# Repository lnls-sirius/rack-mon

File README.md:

# Controls Group rack monitoring system

## Index

- [Description](https://github.com/lnls-sirius/rack-mon#description)
- [Software](https://github.com/lnls-sirius/rack-mon#software)
- [Installation](https://github.com/lnls-sirius/rack-mon#installation)
- [Versions](https://github.com/lnls-sirius/rack-mon#versions)

## Description

   This project is a hardware and software solution for Sirius cabinets monitoring based in a NXP's development platform, FRDM-KL25z, and SPIxxCON bus present  on Controls Group SERIALxxCON hardware. The designed baseboard for NXP development  platform  contains  the  necessary  peripherals  to  acquire  information  such  as temperature, humidity, fan status, door status and supply voltage in order to predict possible system failures and evaluate its correlation with the acquired data.

   It also contains an adapter that [enables this project to work with mbed LPC1768](https://github.com/lnls-sirius/rack-mon/tree/master/KL25Z_to_LPC1768) in instead of KL25z.

## Software

### [KL25z](https://github.com/lnls-sirius/rack-mon/blob/master/Software/SlaveSW/SlaveKL25Z.c)

   A C program written through Mbed's platform divided in 3 modes:

   * Read mode

   An interruption associated with the rising border of Slave Select signal. In this interruption the microcontroller reads the SPI buffer and if a command other than zero is found stores the command.

   * Buffer copy

   The main loop in the program, where the strings are copied to the "answer" buffer according to the code read in the Read Mode.

   * Ansawer mode

   Another interruption associated with Slave Select signal, but this happens in the falling border of the signal. This is where the board replies the requested value through SPI.

### [LPC1768](https://github.com/lnls-sirius/rack-mon/blob/master/KL25Z_to_LPC1768/Software/SlaveLPC1768.cpp)

   When using LPC1768 in instead of KL25Z a few things change. The principle is still the same: reading from the SPI, copying to a answer buffer and responding through SPI but here the program doesn't work with interruptions, everything happens inside the main loop.

   The microcontroller reads the SPI and if there is any request enters a switch-case conditional. If the command corresponds to any of the known commands, LPC1768 responds accordingly.

### [BeagleBone Black](https://github.com/lnls-sirius/rack-mon/blob/master/Software/MasterSW/MasterBBB.py)

   A Python script responsible for the communication between BeagleBone Black and KL25z (or LPC1768) through SPI and for providing the data to multiple workstations through TCP/IP sockets.

#### Configuration and Python3 module

In order to operate the board you should first do the following configurations in your SERIALxxCON:

- Configure the SPI buses with:

```shell
config-pin P9_17 spi_cs
config-pin P9_21 spi
config-pin P9_18 spi
config-pin P9_22 spi_sclk
```
- Write the previous commands on `/etc/rc.local` if desired

- Stop bbb-function script with:

```shell
systemctl stop bbb-function
```
- Disable bbb-function if desired:

```shell
systemctl disable bbb-function
```

A python3 module was developed in order to simplify the SPI requests to the board. The [Very Simple Protocol](https://gitlab.cnpem.br/vitor.santos/racks/blob/master/Software/MasterSW/vsp.py) module functions are:

- send(char, timeout_ms = 1)

sends a character to the monitoring board and returns a string with its response

- get(\*args)

sends multiple characters to the monitoring board and returns a list with it's response _in order_

- get_all()

returns a list with values for supply voltage, fan status, DHT's temperature measurement, fan current, humidity, LM35's temperature measurement, back door status and front door status _in that order_

- get_LM35()

returns LM35's temperature measurement

- get_DHT()

returns the boards DHT's temperature measurement

- get_humidity()

returns humidity value

- get_fdoor()

returns front door status

- get_bdoor()

returns back door status

- get_fanstat()

returns fan status

- get_current()

returns current measurement

- get_voltage()

returns supply voltage

- isBoard()

works only with LPC1768 and returns the software version, if "None" is returned it means probably there's no board connected or it's a KL25z with software version < v1.60

If using KL25z in instead of LPC1768, lines containing "for i in range (10)" should be changed to "for i in range(11)".

## Installation

   * Remove the back panel of SERIALxxCON box and place the SPIxxCON - RJ25 adapter. Connect the serial cable and close the box with the [new back panel](https://gitlab.cnpem.br/vitor.santos/racks/blob/master/Hardware/SPIxxCON_BackPanel.pdf).

   * Plug one end of the power cable into the black plug and the other end into the power strip.

   * Unplug the fan power cable from the power strip and plug it into the box's red power outlet.

   * Fix the magnetic sensors to their mountings and place them close to the door, in the upper part of the cabinet. Place the neodymium magnet on the cabinet door in a way that when its closed the magnet is close to the magnetic sensor.

   * Place the DHT11 humidity sensor close to the box.

   * Place the LM35 temperature sensor wherever you want.

   * Connect all the sensors to their respective connectors.

## Versions

Each prototype version is named as follows:
_vX.YZ_
- X: hardware version (even numbers are in-house manufactured prototypes).
- Y: prototype hardware version.
- Z: software version.

Available KL25z software versions:

- [v0.60](https://github.com/lnls-sirius/rack-mon/blob/master/Software/SlaveSW/SlaveKL25Z.c)
- ~~v0.58~~
- ~~v0.55~~
- ~~v0.5~~
- ~~v0.4~~

Available LPC1768 software versions:

- [v1.60](https://github.com/lnls-sirius/rack-mon/blob/master/KL25Z_to_LPC1768/Software/SlaveLPC1768.cpp)

Previous versions can be found on these repositories: [KL25Z](https://os.mbed.com/users/vitorsp/code/rack-monitoring-system/) and [LPC1768](https://os.mbed.com/users/vitorsp/code/rack-monitoring-system-LPC1768/).

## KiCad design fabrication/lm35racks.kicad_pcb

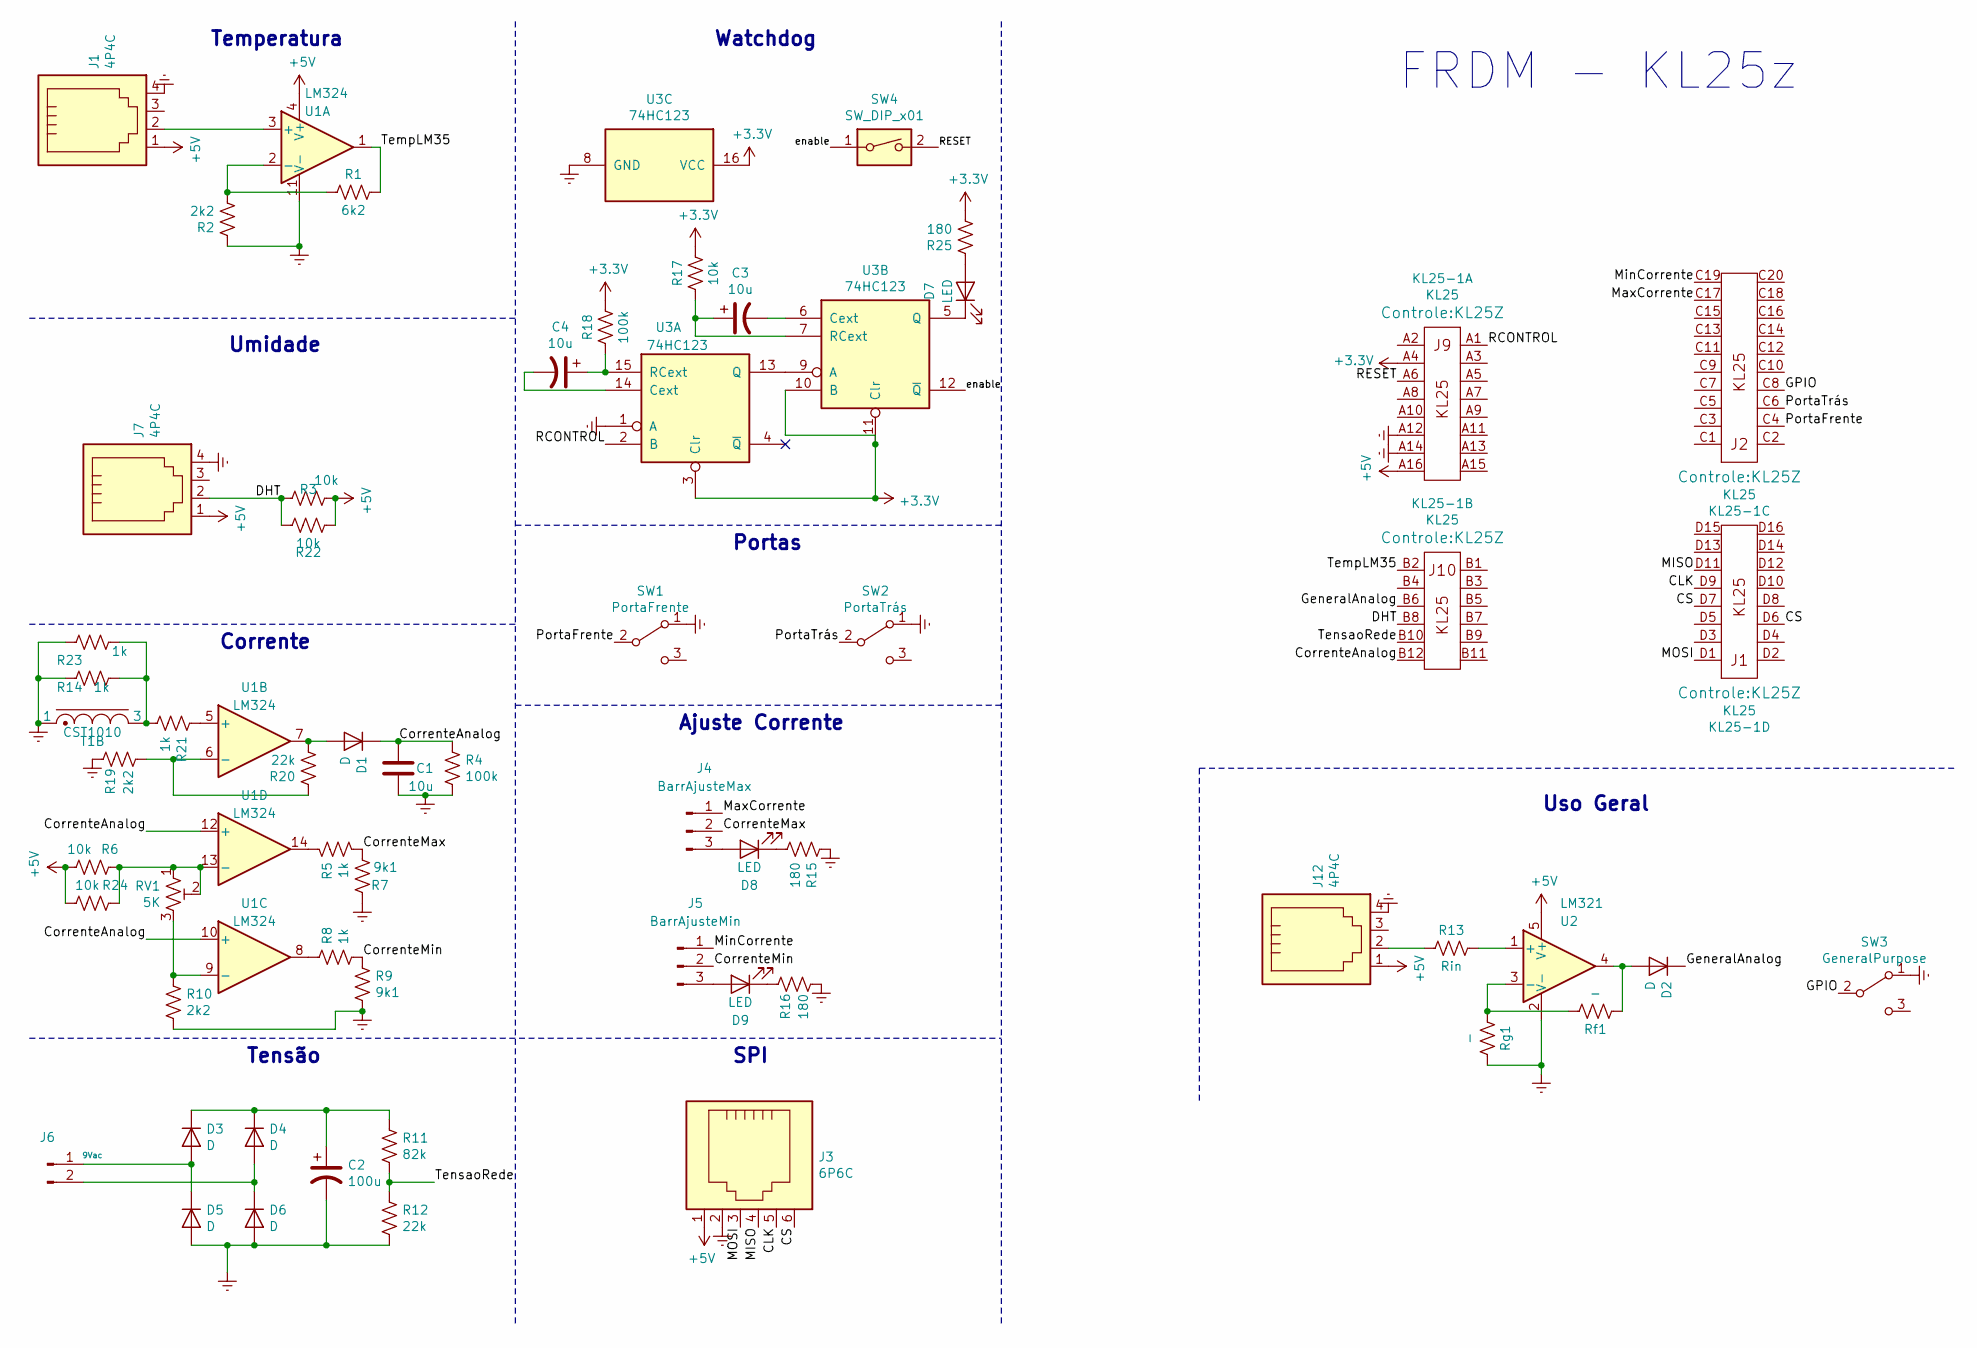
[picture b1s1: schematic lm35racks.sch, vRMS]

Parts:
C1: 10u; C_0805_2012Metric_Pad1.15x1.40mm_HandSolder
C2: 100u; C_Elec_6.3x7.7
C3, C4: 10u; C_1206_3216Metric_Pad1.42x1.75mm_HandSolder
D1, D2, D3, D4, D5, D6: D; D_0805_2012Metric_Pad1.15x1.40mm_HandSolder
D7, D8, D9: LED; D_0805_2012Metric_Pad1.15x1.40mm_HandSolder
J1, J7, J12: 4P4C; RJ11-4P4C-HIROSE_2
J3: 6P6C; RJ25(vitor)
J4: BarrAjusteMax; PinHeader_1x03_P2.54mm_Vertical
J5: BarrAjusteMin; PinHeader_1x03_P2.54mm_Vertical
J6: 9Vac; Borne KRE
KL25-1: KL25; KL25Z
R1: 6k2; R_0805_2012Metric_Pad1.15x1.40mm_HandSolder
R2, R10, R19: 2k2; R_0805_2012Metric_Pad1.15x1.40mm_HandSolder
R3, R6, R17, R22, R24: 10k; R_0805_2012Metric_Pad1.15x1.40mm_HandSolder
R4, R18: 100k; R_0805_2012Metric_Pad1.15x1.40mm_HandSolder
R5, R8, R14, R21, R23: 1k; R_0805_2012Metric_Pad1.15x1.40mm_HandSolder
R7, R9: 9k1; R_0805_2012Metric_Pad1.15x1.40mm_HandSolder
R11: 82k; R_0805_2012Metric_Pad1.15x1.40mm_HandSolder
R12, R20: 22k; R_0805_2012Metric_Pad1.15x1.40mm_HandSolder
R13: Rin; R_0805_2012Metric_Pad1.15x1.40mm_HandSolder
R15, R16, R25: 180; R_0805_2012Metric_Pad1.15x1.40mm_HandSolder
RV1: 5K; Potentiometer_Bourns_3266Y_Vertical
Rf1: -; R_0805_2012Metric_Pad1.15x1.40mm_HandSolder
Rg1: -; R_0805_2012Metric_Pad1.15x1.40mm_HandSolder
SW1: PortaFrente; Borne KRE
SW2: PortaTrás; Borne KRE
SW3: GeneralPurpose; Borne KRE
SW4: SW_DIP_x01; DIPSwitchSMD_1pos
T1: CST1010; CST
U1: LM324; SOIC-14_3.9x8.7mm_P1.27mm
U2: LM321; SOT-23-5
U3: 74HC123; SOIC-16W_5.3x10.2mm_P1.27mm

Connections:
+3V3: KL25-1.A4, R17.2, R18.2, R25.2, U3.3 (Clr), U3.10 (B), U3.11 (Clr), U3.16 (VCC)
+5V: J1.1, J3.1, J7.1, J12.1, KL25-1.A16, R3.2, R6.1, R22.2, R24.2, U1.4 (V+), U2.5 (V+)
/CLK: J3.5, KL25-1.D9
/CS: J3.6, KL25-1.D6, KL25-1.D7
/CorrenteAnalog: C1.1, D1.1 (K), KL25-1.B12, R4.1, U1.10 (+), U1.12 (+)
/CorrenteMax: J4.2, R5.2, R7.2
/CorrenteMin: J5.2, R8.2, R9.1
/DHT: J7.2, KL25-1.B8, R3.1, R22.1
/GPIO: KL25-1.C8, SW3.2 (B)
/GeneralAnalog: D2.1 (K), KL25-1.B6
/MISO: J3.4, KL25-1.D11
/MOSI: J3.3, KL25-1.D1
/MaxCorrente: J4.1, KL25-1.C17
/MinCorrente: J5.1, KL25-1.C19
/PortaFrente: KL25-1.C4, SW1.2 (B)
/PortaTrás: KL25-1.C6, SW2.2 (B)
/RCONTROL: KL25-1.A1, U3.2 (B)
/RESET: KL25-1.A6, SW4.2
/TempLM35: KL25-1.B2, R1.2, U1.1
/TensaoRede: KL25-1.B10, R11.2, R12.1
/enable: SW4.1, U3.12 (~Q)
Earth: C1.2, C2.2, D5.2 (A), D6.2 (A), J1.4, J3.2, J7.4, J12.4, KL25-1.A12, KL25-1.A14, R2.1, R4.2, R7.1, R9.2, R10.2, R12.2, R14.1, R15.1, R16.2, R19.1, R23.1, Rg1.2, SW1.1 (A), SW2.1 (A), SW3.1 (A), T1.1, U1.11 (V-), U2.2 (V-), U3.1 (A), U3.8 (GND); also elsewhere on the board
unnamed: C2.1, D3.1 (K), D4.1 (K), R11.1
unnamed: C3.1, R17.1, U3.7 (RCext)
unnamed: C3.2, U3.6 (Cext)
unnamed: C4.1, R18.1, U3.15 (RCext)
unnamed: C4.2, U3.14 (Cext)
unnamed: D1.2 (A), R20.2, U1.7
unnamed: D2.2 (A), Rf1.1, U2.4
unnamed: D3.2 (A), D5.1 (K), J6.1
unnamed: D4.2 (A), D6.1 (K), J6.2
unnamed: D7.1 (K), U3.5 (Q)
unnamed: D7.2 (A), R25.1
unnamed: D8.1 (K), R15.2
unnamed: D8.2 (A), J4.3
unnamed: D9.1 (K), R16.1
unnamed: D9.2 (A), J5.3
unnamed: J1.2, U1.3 (+)
unnamed: J12.2, R13.1
unnamed: R1.1, R2.2, U1.2 (-)
unnamed: R5.1, U1.14
unnamed: R8.1, U1.8
unnamed: R10.1, RV1.3, U1.9 (-)
unnamed: R13.2, U2.1 (+)
unnamed: R14.2, R21.2, R23.2, T1.3
unnamed: R19.2, R20.1, U1.6 (-)
unnamed: R21.1, U1.5 (+)
unnamed: R6.2, R24.1, RV1.1, RV1.2, U1.13 (-)
unnamed: Rf1.2, Rg1.1, U2.3 (-)
unnamed: U3.9 (A), U3.13 (Q)

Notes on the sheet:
Temperatura
Umidade
Corrente
Tensão
FRDM - KL25z
SPI
Ajuste Corrente
Portas
Uso Geral
Watchdog

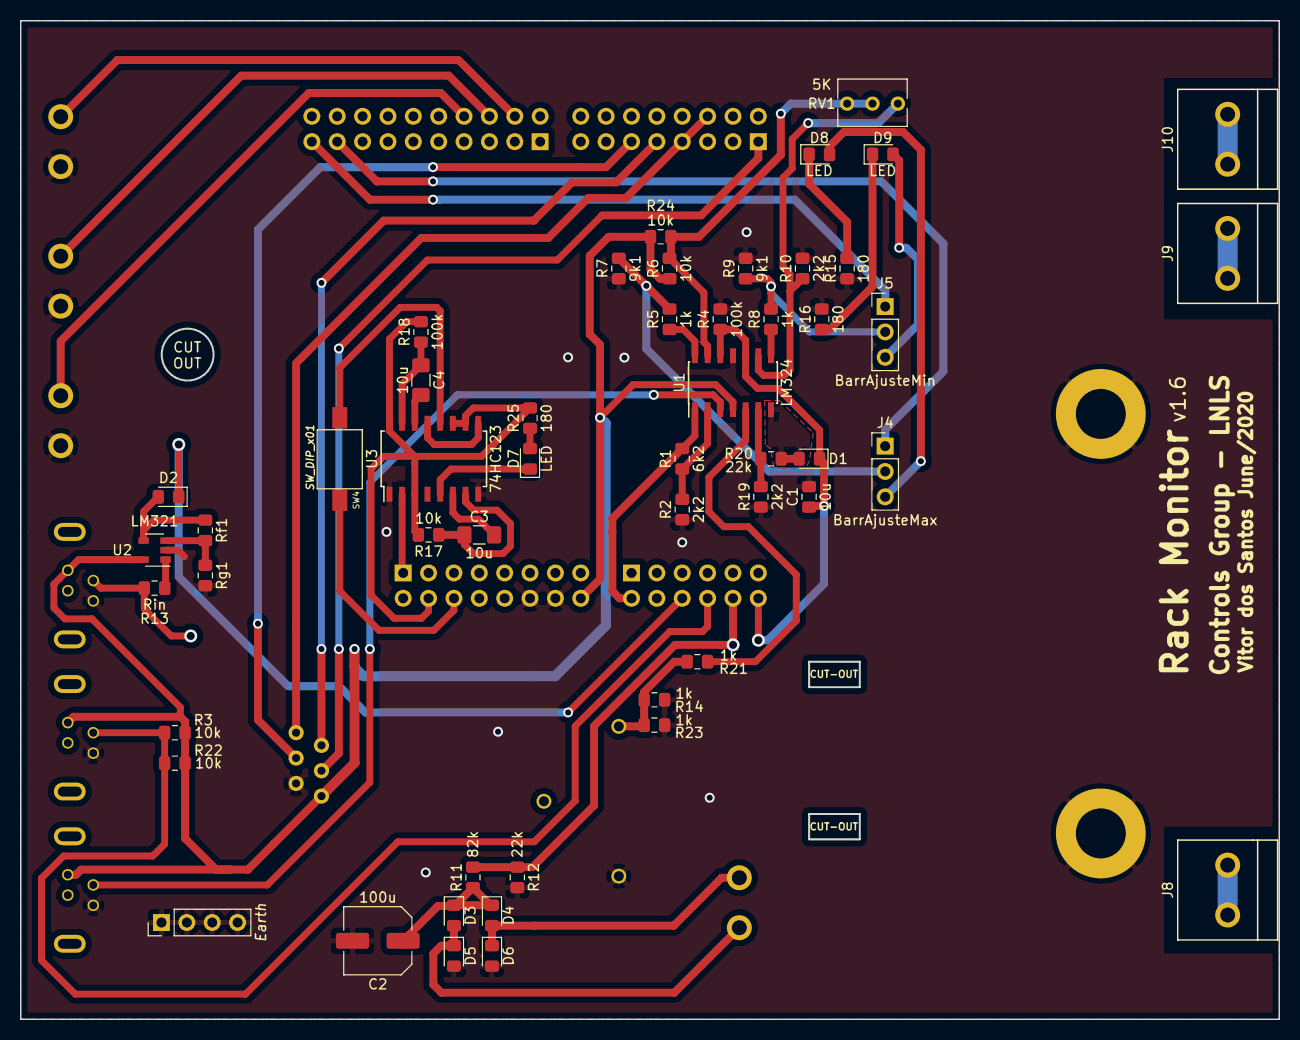
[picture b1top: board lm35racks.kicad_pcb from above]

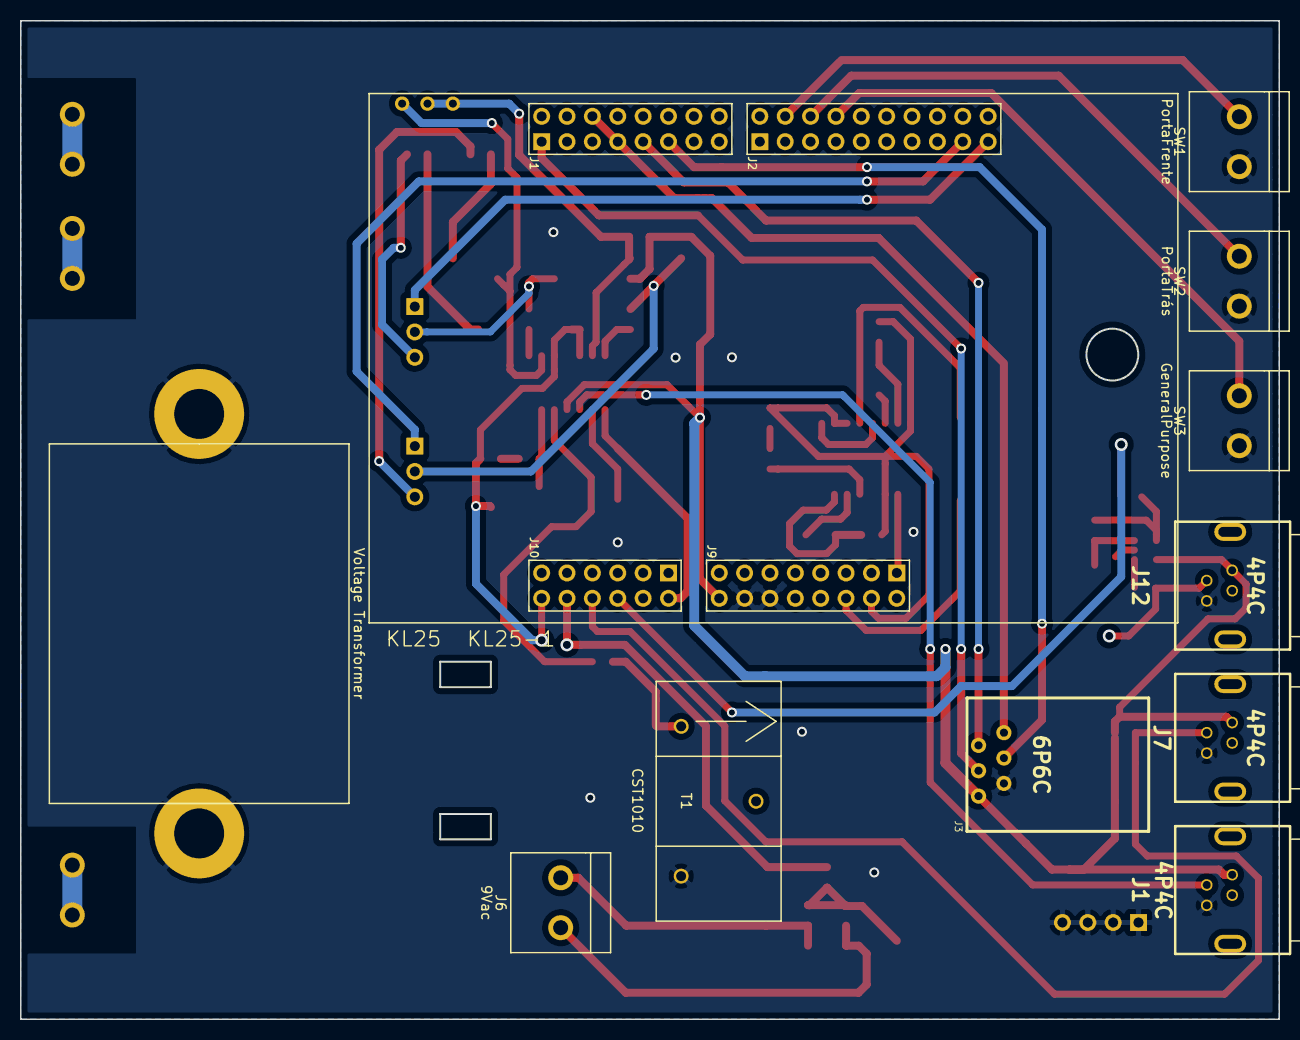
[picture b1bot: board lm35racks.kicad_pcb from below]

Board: 2 copper layers, 126.0 x 99.9 mm, 62 parts (10 on the bottom side), 50 nets.

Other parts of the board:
Earth Header: Earth; PinHeader_1x04_P2.54mm_Vertical
J8: TrafoTensão; Borne KRE
J9, J10: TrafoCorrente; Borne KRE
TV*: Voltage Transformer; TrafoVesteves

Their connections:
Earth: Earth Header.1, Earth Header.2, Earth Header.3, Earth Header.4, TV*.1, TV*.2; also elsewhere on the board

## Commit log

2020-12-01 README update
2020-12-17 v1.6 HW with silk-screen
2020-12-17 4P4C spacement adjusted
